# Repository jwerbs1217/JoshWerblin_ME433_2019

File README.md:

Joshua Werblin
9 April 2019
--------

This repository will be filled with the files for ME433: Advanced Mechatronics for Winter 2019 Quarter at Northwestern University. Assignments can be found at https://github.com/ndm736/ME433_2019/

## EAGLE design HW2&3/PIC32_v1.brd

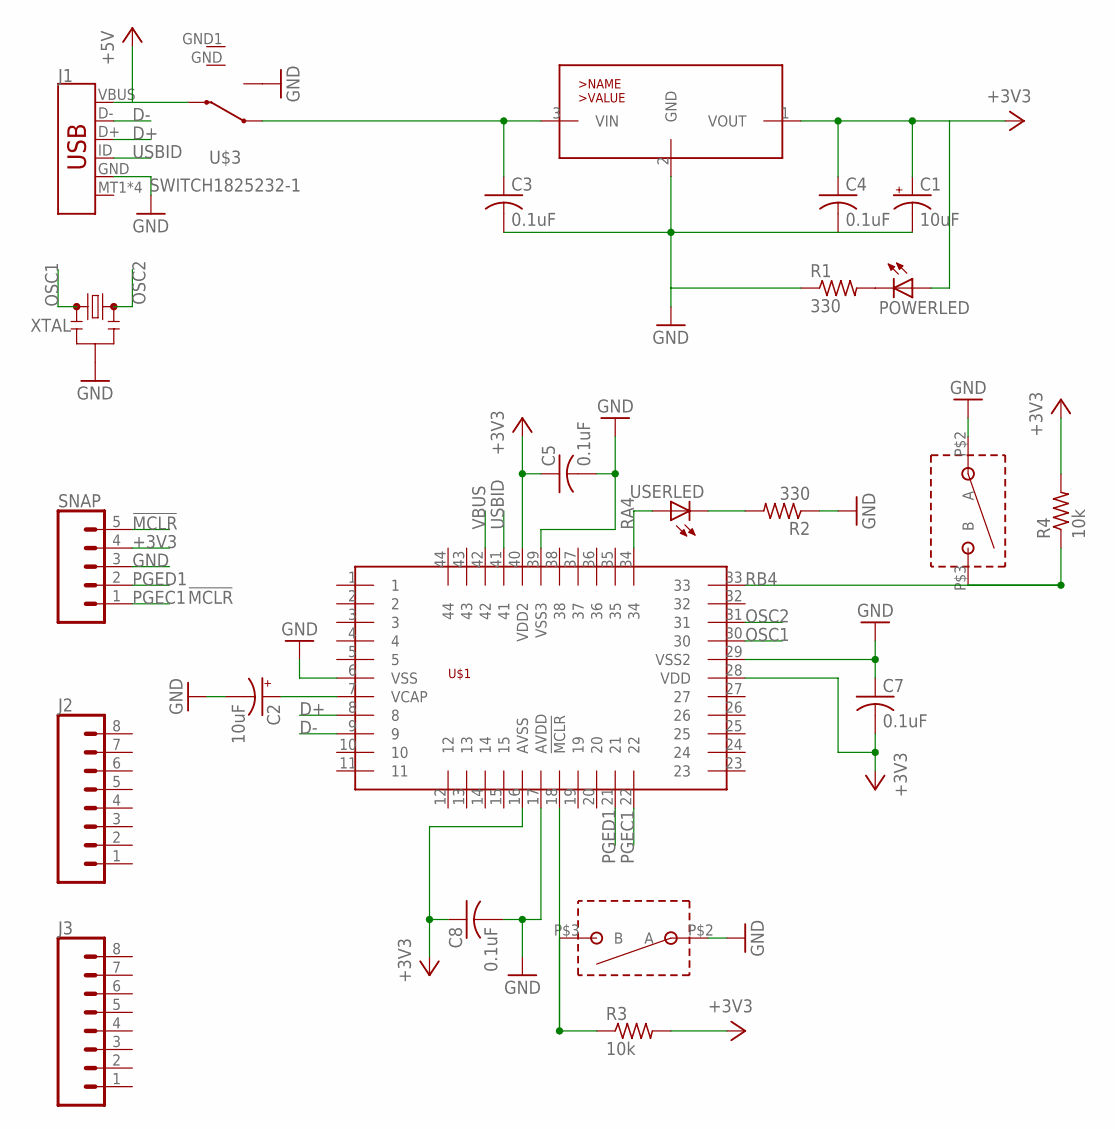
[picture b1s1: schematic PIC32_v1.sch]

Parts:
C1, C2: 10uF; TAP5-50
C3, C4, C5, C7, C8: 0.1uF; C025-024X044
J1: USB_MICRO-B_SMT; USB-MICROB
J2, J3: CONN_08"; 1X08
POWERLED: LED3MM
R1, R2: 330; 0309/12
R3, R4: 10k; 0309/12
SNAP: CONN_05; 1X05
U$1: PIC32MX170F256D-TQFP44; TQFP44
U$2, U$4: PUSHBUTTON; PBEVQ-11A07K
U$3: SWITCH1825232-1; 1825232-1
USERLED: LED3MM
VREGULATOR: L4931-TO92; TO92
XTAL: RESONATORPTH-7.6X3.8; RESONATOR-PTH-7.6X3.8

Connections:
!MCLR: R3.1, SNAP.5, U$1.18 (!MCLR), U$4.P$3 (B)
+3V3: C1.+, C4.1, C5.1, C7.2, C8.1, POWERLED.A, R3.2, R4.2, SNAP.4, U$1.16 (AVSS), U$1.28 (VDD), U$1.40 (VDD2), VREGULATOR.1 (VOUT)
+5V: J1.VBUS, U$3.2
D+: J1.D+, U$1.8
D-: J1.D-, U$1.9
GND: C1.-, C2.-, C3.2, C4.2, C5.2, C7.1, C8.2, J1.GND, R1.1, R2.1, SNAP.3, U$1.6 (VSS), U$1.17 (AVDD), U$1.29 (VSS2), U$1.39 (VSS3), U$2.P$2 (A), U$3.1, U$4.P$2 (A), VREGULATOR.2 (GND), XTAL.2
unnamed: POWERLED.K (C), R1.2
unnamed: R2.2, USERLED.K (C)
unnamed: C3.1, U$3.3, VREGULATOR.3 (VIN)
unnamed: C2.+, U$1.7 (VCAP)
OSC1: U$1.30, XTAL.1
OSC2: U$1.31, XTAL.3
PGEC1: SNAP.1, U$1.22
PGED1: SNAP.2, U$1.21
RA4: U$1.34, USERLED.A
RB4: R4.1, U$1.33, U$2.P$3 (B)
USBID: J1.ID, U$1.41
VBUS: U$1.42

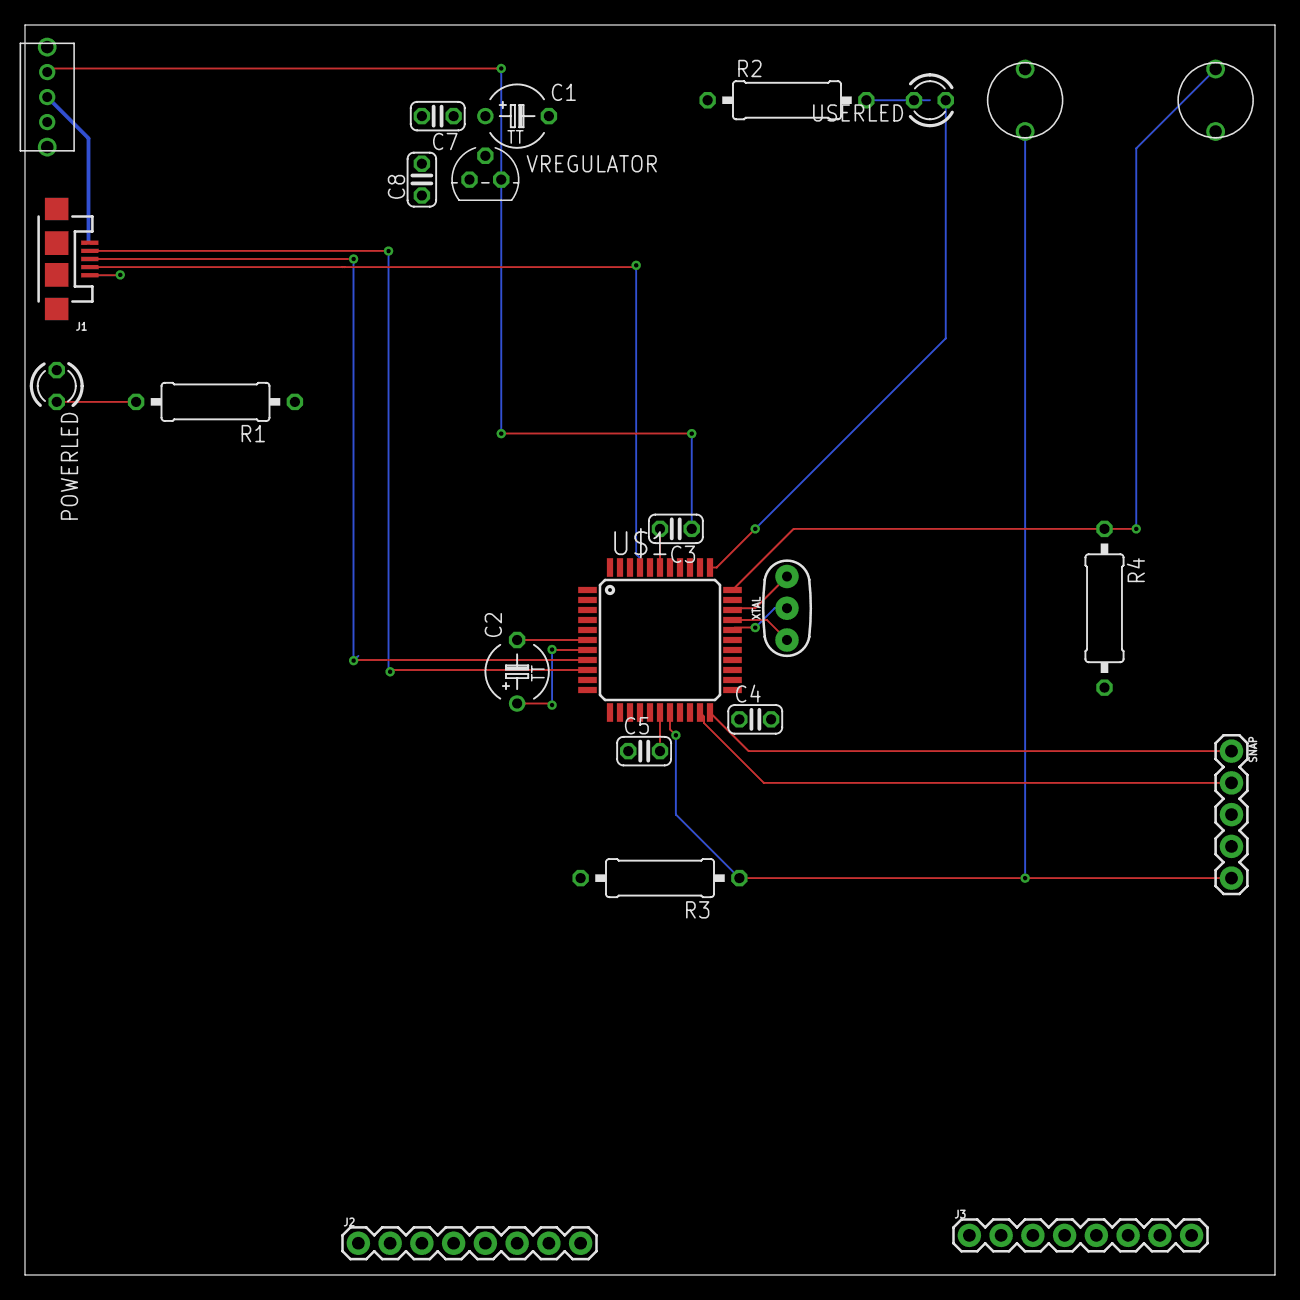
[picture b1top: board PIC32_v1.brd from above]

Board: 2 copper layers, 100.0 x 100.0 mm, 23 parts (0 on the bottom side), 17 nets.

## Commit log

2019-04-09 Create README.md
    My first commit!
2019-04-09 Update README.md
    Edit readme
2019-04-09 Create PIC circuit diagram.jpg
    PIC circuit diagram
2019-04-09 V Regulator images
    V regulator with and without the capacitors
2019-04-09 PIC on breadboard image
2019-04-10 HW1 skeleton
    Blank files for HW1 project
2019-04-10 Added initialization to main.c
2019-04-10 Added light blinking but timing is wrong
2019-04-10 Finished HW1 code
2019-04-10 HW1 final parts
    Includes nScope picture showing 1kHz square qave
2019-04-10 HW1 demo video
2019-04-12 1st PCB lib, sch, and brd
2019-04-12 Structuring code for HW4
2019-04-12 Added math to calculate waveforms
2019-04-14 First test of SPI/DAC code
2019-04-14 Moved files into MPLAB IDE
2019-04-16 HW4 circuit drawing
2019-04-18 HW4 and HW1 edits
    Triangle wave works but sine does not for HW4, HW1 I just changed a couple settings
2019-04-18 Finished HW4
    Final HW4 code and image of scope
2019-04-22 First edits
2019-04-23 Finished HW5
2019-04-23 HW5 circuit and video
2019-04-23 changed I2C2BRG to be correct
2019-04-24 Beginning HW6
2019-04-25 Finished HW6
2019-04-25 Video of working LCD screen
2019-04-28 The IMU works! Kind of...
2019-04-28 Changed a comment
2019-04-28 IMU works! But realizing shortcomings of my bar drawing function
2019-04-28 Finished HW7
2019-04-28 HW6 demo video
2019-04-28 HW6 demo
2019-04-28 Finished HW8
2019-05-06 Included 2nd half of HW8
2019-05-08 HW9 touch screen pixels
2019-05-08 Finished HW9
2019-05-08 Updated finished HW9
2019-05-13 Generated HW10 code
2019-05-13 HW9 changed comment
2019-05-13 Fixed USB timing issue
2019-05-13 added imu
2019-05-14 Finished HW10
2019-05-26 HW10 now includes HW11
2019-05-27 HW11 finished
2019-05-27 Finished HW12
2019-05-30 HW13 laser cut
2019-05-30 Finished HW13 by adding wheel design
2019-06-01 HW15 start
2019-06-09 HW11 added figures
2019-06-09 Update 15
2019-06-10 Finished LCD RGB plotting, motor stuff not working
2019-06-10 PWM works; timer int doesn't
2019-06-10 HW15 done
2019-06-14 Finished hw14
2019-06-14 HW16 does not successfully follow line :(

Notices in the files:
parts and their libraries:
SparkFun-Connectors: Licensing: Creative Commons ShareAlike 4.0 International - https://creativecommons.org/licenses/by-sa/4.0
